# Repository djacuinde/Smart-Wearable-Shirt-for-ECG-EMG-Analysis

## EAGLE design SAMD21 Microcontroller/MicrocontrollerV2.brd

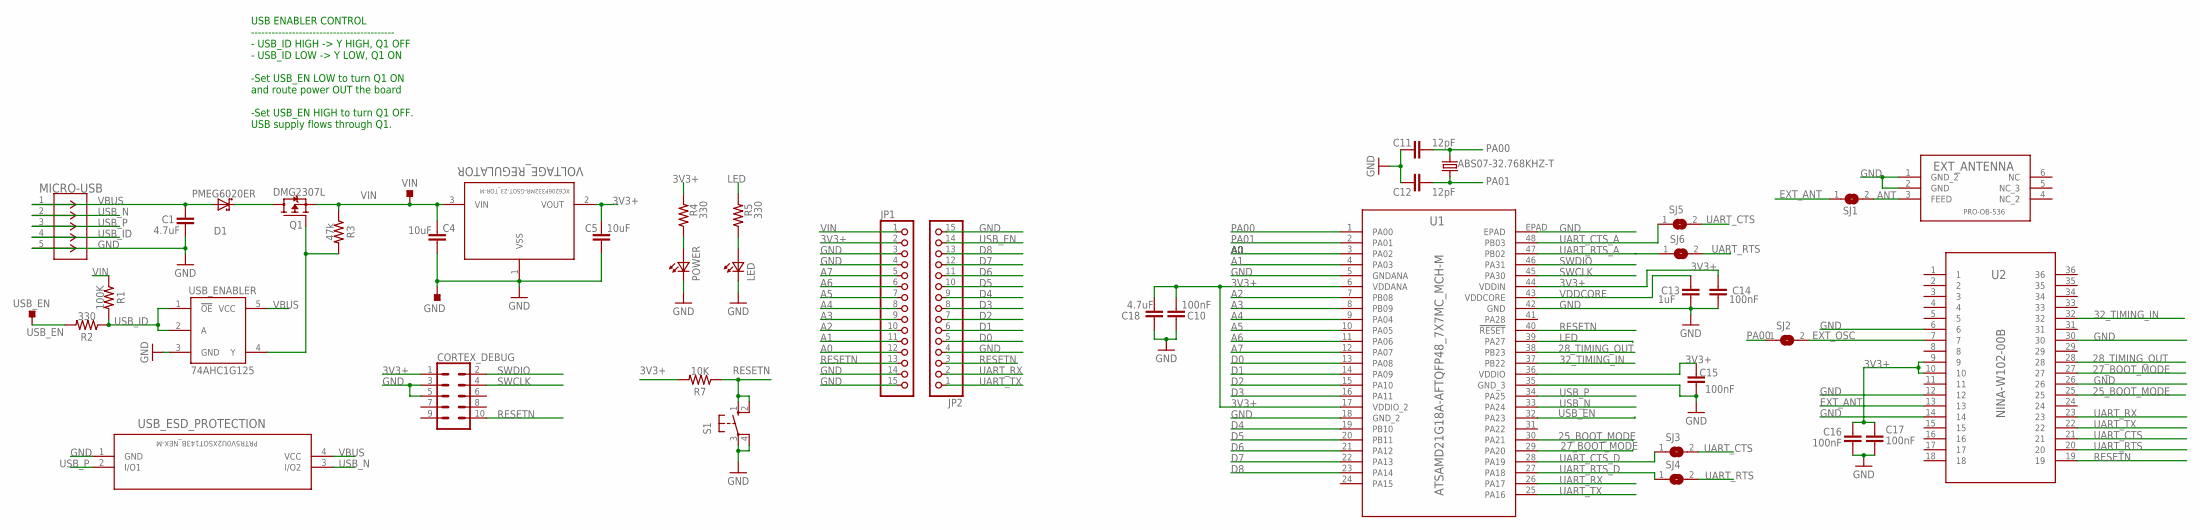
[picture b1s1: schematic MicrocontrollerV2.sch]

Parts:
ABS07-32.768KHZ-T: 32.768KHz; ABS07-32.768KHZ-T
C1, C18: 4.7uF; CAPC1608X85
C4, C5: 10uF; CAPC1608X85
C10, C14, C15, C16, C17: 100nF; CAPC1608X85
C11, C12: 12pF; CAPC1608X85
C13: 1uF; CAPC1608X85
CORTEX_DEBUG: CONN_05X2NO_SILK; 2X5_NOSILK
D1: PMEG6020ER; SOD123W
EXT_ANTENNA: PRO-OB-536; PRO-OB-536_PAB
GND: TESTPOINT_TPS-SMD-10SN; TESTPOINT_SMD-10SN
JP1, JP2: PINHD-1X15; 1X15
LED: HSMR-C190; 0603
MICRO-USB: ZX62-AB-5PA(31); CONN5_ZX62-AB-5PA_HIR
POWER: HSMR-C190; 0603
Q1: DMG2307L; SOT96P240X110-3N
R1: 100K; RESC1608X60
R2, R4, R5: 330; RESC1608X60
R3: 47k; RESC1608X60
R7: 10K; RESC1608X60
S1: PTS525SK08; SM08
SJ1, SJ2, SJ3, SJ4, SJ5, SJ6: SJ
U1: ATSAMD21G18A-AFTQFP48_7X7MC_MCH-M; TQFP48_7X7MC_MCH-M
U2: NINA-W102-00B; QFN_W151-00B_UBL
USB_EN: TESTPOINT_TPS-SMD-10SN; TESTPOINT_SMD-10SN
USB_ENABLER: 74AHC1G125; SOT23-5L
USB_ESD_PROTECTION: PRTR5V0U2XSOT143B_NEX-M; SOT143B_NEX-M
VIN: TESTPOINT_TPS-SMD-10SN; TESTPOINT_SMD-10SN
VOLTAGE_REGULATOR: XC6206P332MR-GSOT-23_TOR-M; SOT-23_TOR-M

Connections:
3V3+: C5.1, C10.2, C14.2, C15.2, C16.1, C17.2, C18.2, CORTEX_DEBUG.1, JP1.2, R4.2, R7.2, U1.6 (VDDANA), U1.17 (VDDIO_2), U1.36 (VDDIO), U1.44 (VDDIN), U2.9, U2.10, VOLTAGE_REGULATOR.2 (VOUT)
25_BOOT_MODE: U1.30 (PA21), U2.25
27_BOOT_MODE: U1.29 (PA20), U2.27
28_TIMING_OUT: U1.38 (PB23), U2.28
32_TIMING_IN: U1.37 (PB22), U2.32
A0: JP1.12, U1.3 (PA02)
A1: JP1.11, U1.4 (PA03)
A2: JP1.10, U1.7 (PB08)
A3: JP1.9, U1.8 (PB09)
A4: JP1.8, U1.9 (PA04)
A5: JP1.7, U1.10 (PA05)
A6: JP1.6, U1.11 (PA06)
A7: JP1.5, U1.12 (PA07)
ANT: EXT_ANTENNA.3 (FEED), SJ1.2
D0: JP2.5, U1.13 (PA08)
D1: JP2.6, U1.14 (PA09)
D2: JP2.7, U1.15 (PA10)
D3: JP2.8, U1.16 (PA11)
D4: JP2.9, U1.19 (PB10)
D5: JP2.10, U1.20 (PB11)
D6: JP2.11, U1.21 (PA12)
D7: JP2.12, U1.22 (PA13)
D8: JP2.13, U1.23 (PA14)
EXT_ANT: SJ1.1, U2.13
EXT_OSC: SJ2.2, U2.7
GND: C1.2, C4.1, C5.2, C10.1, C11.1, C12.1, C13.1, C14.1, C15.1, C16.2, C17.1, C18.1, CORTEX_DEBUG.3, CORTEX_DEBUG.5, EXT_ANTENNA.1 (GND_2), EXT_ANTENNA.2 (GND), GND.TP, JP1.3, JP1.4, JP1.14, JP1.15, JP2.4, JP2.15, LED.1 (K2), MICRO-USB.5, POWER.1 (K2), S1.3, S1.4 (P1), U1.5 (GNDANA), U1.18 (GND_2), U1.35 (GND_3), U1.42 (GND), U1.EPAD, U2.6, U2.12, U2.14, U2.26, U2.30, USB_ENABLER.3 (GND), USB_ESD_PROTECTION.1 (GND), VOLTAGE_REGULATOR.1 (VSS)
LED: R5.2, U1.39 (PA27)
unnamed: LED.2 (A2), R5.1
unnamed: POWER.2 (A2), R4.1
unnamed: D1.1 (K), Q1.3 (D)
unnamed: Q1.1 (G), R3.2, USB_ENABLER.4 (Y)
PA00: ABS07-32.768KHZ-T.2, C11.2, SJ2.1, U1.1 (PA00)
PA01: ABS07-32.768KHZ-T.1, C12.2, U1.2 (PA01)
RESETN: CORTEX_DEBUG.10, JP1.13, JP2.3, R7.1, S1.1 (S), S1.2 (S1), U1.40 (!RESET), U2.19
SWCLK: CORTEX_DEBUG.4, U1.45 (PA30)
SWDIO: CORTEX_DEBUG.2, U1.46 (PA31)
UART_CTS: SJ3.2, SJ5.2, U2.21
UART_CTS_A: SJ5.1, U1.48 (PB03)
UART_CTS_D: SJ3.1, U1.28 (PA19)
UART_RTS: SJ4.2, SJ6.2, U2.20
UART_RTS_A: SJ6.1, U1.47 (PB02)
UART_RTS_D: SJ4.1, U1.27 (PA18)
UART_RX: JP2.2, U1.26 (PA17), U2.23
UART_TX: JP2.1, U1.25 (PA16), U2.22
USB_EN: JP2.14, R2.2, U1.32 (PA23), USB_EN.TP
USB_ID: MICRO-USB.4, R1.2, R2.1, USB_ENABLER.1 (!OE), USB_ENABLER.2 (A)
USB_N: MICRO-USB.2, U1.33 (PA24), USB_ESD_PROTECTION.3 (I/O2)
USB_P: MICRO-USB.3, U1.34 (PA25), USB_ESD_PROTECTION.2 (I/O1)
VBUS: C1.1, D1.2 (A), MICRO-USB.1, USB_ENABLER.5 (VCC), USB_ESD_PROTECTION.4 (VCC)
VDDCORE: C13.2, U1.43 (VDDCORE)
VIN: C4.2, JP1.1, Q1.2 (S), R1.1, R3.1, VIN.TP, VOLTAGE_REGULATOR.3 (VIN)

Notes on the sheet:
USB ENABLER CONTROL ------------------------------------------ - USB_ID HIGH -> Y HIGH, Q1 OFF - USB_ID LOW -> Y LOW, Q1 ON -Set USB_EN LOW to turn Q1 ON and route power OUT the board -Set USB_EN HIGH to turn Q1 OFF. USB supply flows through Q1.

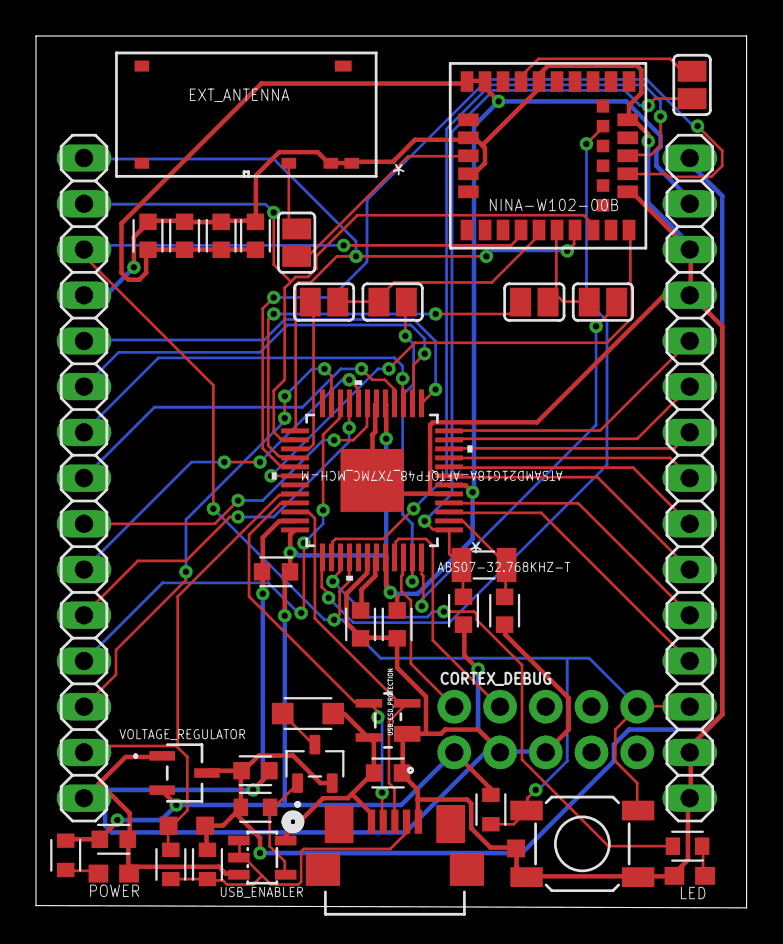
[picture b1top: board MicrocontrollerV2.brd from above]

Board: 2 copper layers, 39.5 x 48.4 mm, 43 parts (0 on the bottom side), 51 nets.

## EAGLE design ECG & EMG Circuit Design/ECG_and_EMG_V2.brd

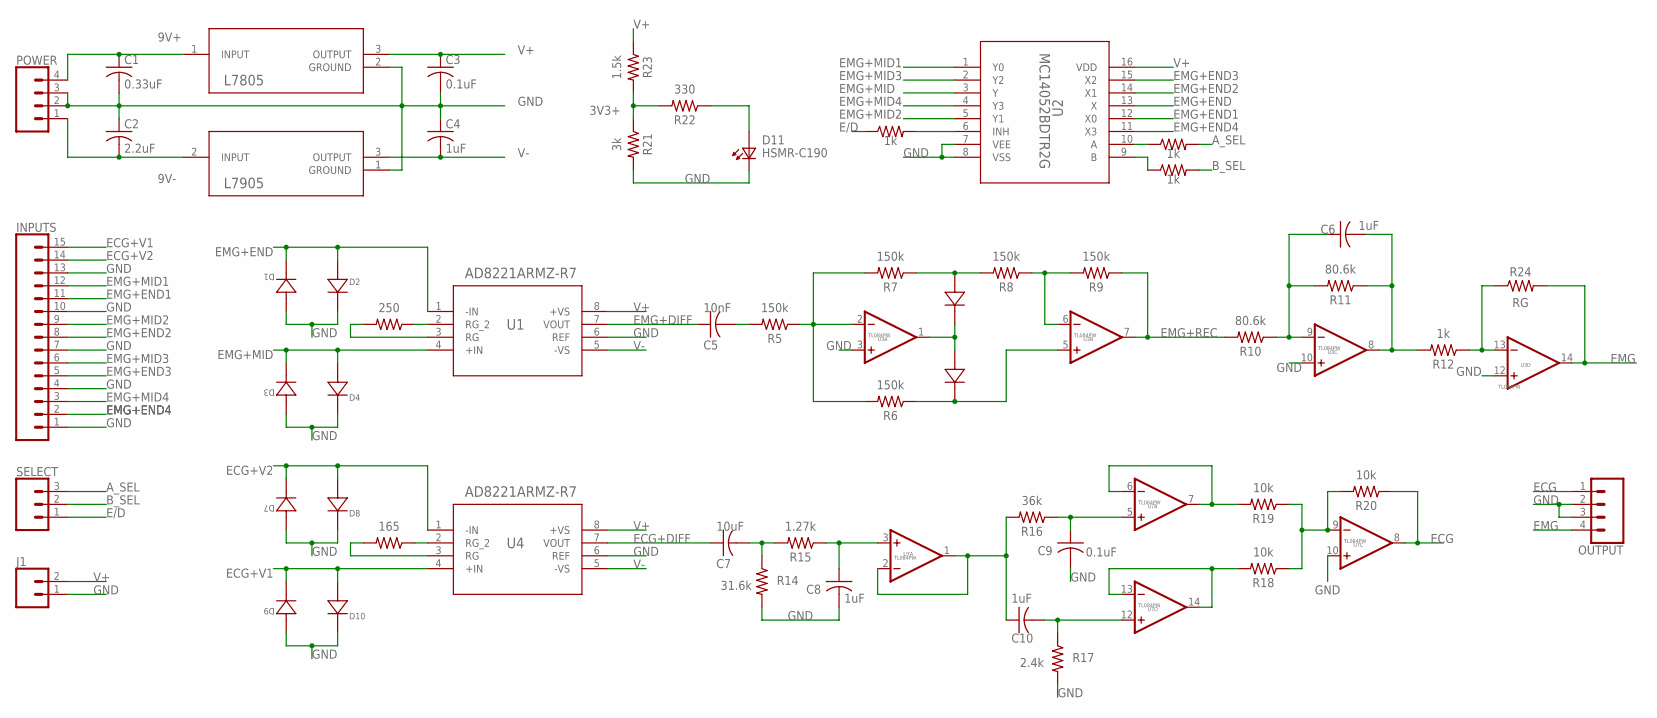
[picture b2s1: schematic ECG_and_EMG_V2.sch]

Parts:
C1: 0.33uF; CAPC2012X110
C2: 2.2uF; CAPC2012X110
C3, C9: 0.1uF; CAPC2012X110
C4, C6, C8, C10: 1uF; CAPC2012X110
C5: 10nF; CAPC2012X110
C7: 10uF; CAPC2012X110
D1, D2, D3, D4, D5, D6, D7, D8, D9, D10: 1N4148W-V-GS08SOD123_VIS-L; SOD123_VIS-L
D11: HSMR-C190; 0603
INPUTS: CONN_15; 1X15
J1: CONN_02; 1X02
L7805: L7805CD2T-TRD2PAK_STM-M; D2PAK_STM-M
L7905: L7905ACD2T-TRD2PAK_STM-M; D2PAK_STM-M
OUTPUT: CONN_04; 1X04
POWER: CONN_04; 1X04
R1, R2, R3, R12: 1k; RESC2012X65
R4: 250; RESC2012X65
R5, R6, R7, R8, R9: 150k; RESC2012X65
R10, R11: 80.6k; RESC2012X65
R13: 165; RESC2012X65
R14: 31.6k; RESC2012X65
R15: 1.27k; RESC2012X65
R16: 36k; RESC2012X65
R17: 2.4k; RESC2012X65
R18, R19, R20: 10k; RESC2012X65
R21: 3k; RESC2012X65
R22: 330; RESC2012X65
R23: 1.5k; RESC2012X65
R24: RG; RESC2012X65
SELECT: CONN_03; 1X03
U1, U4: AD8221ARMZ-R7; RM_8_ADI
U2: MC14052BDTR2G; TSSOP-16_ONS
U3, U7: TL084PW; TSSOP14

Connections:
3V3+: R21.1, R22.2, R23.2
9V+: C1.1, L7805.1 (INPUT), POWER.4
9V-: C2.2, L7905.2 (INPUT), POWER.1
A_SEL: R2.2, SELECT.3
B_SEL: R3.2, SELECT.2
E/D: R1.1, SELECT.1
ECG: OUTPUT.1, R20.1, U7.8 (OUT)
ECG+DIFF: C7.1, U4.7 (VOUT)
ECG+V1: D9.1, D10.2, INPUTS.15, U4.4 (+IN)
ECG+V2: D7.1, D8.2, INPUTS.14, U4.1 (-IN)
EMG: OUTPUT.4, R24.2, U3.14 (OUT)
EMG+DIFF: C5.1, U1.7 (VOUT)
EMG+END: D1.1, D2.2, U1.1 (-IN), U2.13 (X)
EMG+END1: INPUTS.11, U2.12 (X0)
EMG+END2: INPUTS.8, U2.14 (X1)
EMG+END3: INPUTS.5, U2.15 (X2)
EMG+END4: INPUTS.2, U2.11 (X3)
EMG+MID: D3.1, D4.2, U1.4 (+IN), U2.3 (Y)
EMG+MID1: INPUTS.12, U2.1 (Y0)
EMG+MID2: INPUTS.9, U2.5 (Y1)
EMG+MID3: INPUTS.6, U2.2 (Y2)
EMG+MID4: INPUTS.3, U2.4 (Y3)
EMG+REC: R9.1, R10.2, U3.7 (OUT)
GND: C1.2, C2.1, C3.2, C4.1, C8.2, C9.2, D1.2, D2.1, D3.2, D4.1, D7.2, D8.1, D9.2, D10.1, D11.1 (K2), INPUTS.1, INPUTS.4, INPUTS.7, INPUTS.10, INPUTS.13, J1.1, L7805.2 (GROUND), L7905.1 (GROUND), OUTPUT.2, OUTPUT.3, POWER.2, POWER.3, R14.2, R17.2, R21.2, U1.6 (REF), U2.7 (VEE), U2.8 (VSS), U3.3 (+IN), U3.10 (+IN), U3.12 (+IN), U4.6 (REF), U7.10 (+IN)
unnamed: R1.2, U2.6 (INH)
unnamed: R2.1, U2.10 (A)
unnamed: R3.1, U2.9 (B)
unnamed: R4.1, U1.2 (RG_2)
unnamed: R4.2, U1.3 (RG)
unnamed: C5.2, R5.2
unnamed: R5.1, R6.2, R7.2, U3.2 (-IN)
unnamed: D6.1, R6.1, U3.5 (+IN)
unnamed: D5.1, D6.2, U3.1 (OUT)
unnamed: D5.2, R7.1, R8.2
unnamed: R8.1, R9.2, U3.6 (-IN)
unnamed: C6.1, R10.1, R11.2, U3.9 (-IN)
unnamed: C6.2, R11.1, R12.2, U3.8 (OUT)
unnamed: R13.1, U4.2 (RG_2)
unnamed: R12.1, R24.1, U3.13 (-IN)
unnamed: R13.2, U4.3 (RG)
unnamed: C7.2, R14.1, R15.2
unnamed: C8.1, R15.1, U7.3 (+IN)
unnamed: C10.1, R16.2, U7.1 (OUT), U7.2 (-IN)
unnamed: C9.1, R16.1, U7.5 (+IN)
unnamed: C10.2, R17.1, U7.12 (+IN)
unnamed: R18.2, U7.13 (-IN), U7.14 (OUT)
unnamed: R19.2, U7.6 (-IN), U7.7 (OUT)
unnamed: R18.1, R19.1, R20.2, U7.9 (-IN)
unnamed: D11.2 (A2), R22.1
V+: C3.1, J1.2, L7805.3 (OUTPUT), R23.1, U1.8 (+VS), U2.16 (VDD), U3.4 (V+), U4.8 (+VS), U7.4 (V+)
V-: C4.2, L7905.3 (OUTPUT), U1.5 (-VS), U3.11 (V-), U4.5 (-VS), U7.11 (V-)

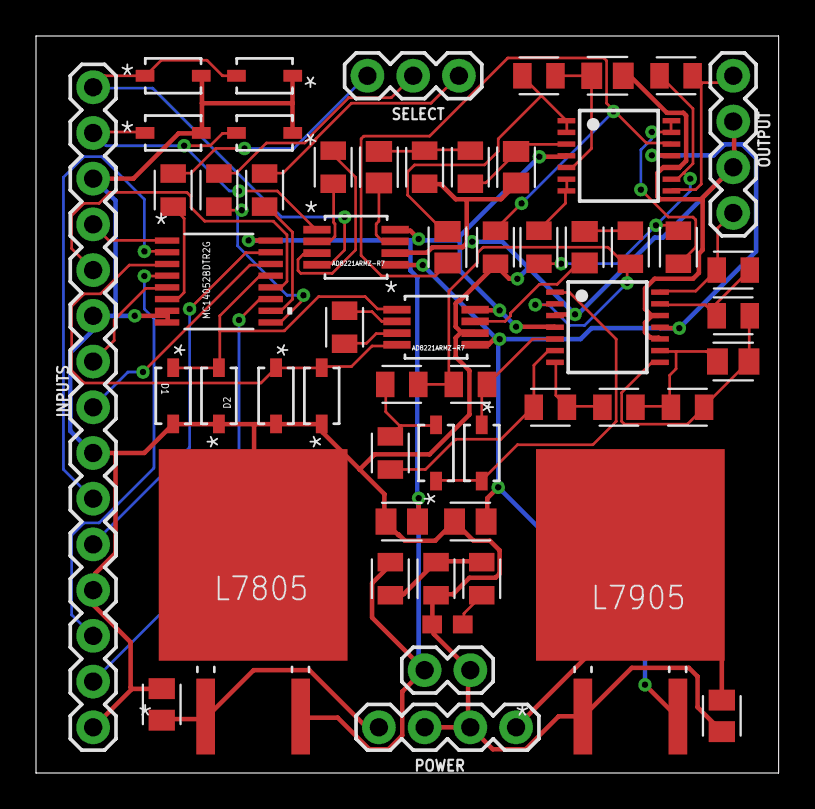
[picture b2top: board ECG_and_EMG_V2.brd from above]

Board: 2 copper layers, 41.3 x 40.9 mm, 57 parts (0 on the bottom side), 51 nets.

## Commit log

2020-12-27 Create EAGLE
2020-12-27 Create SAMD21 Microcontroller
2020-12-27 Create 1
2020-12-27 Rename MicrocontrollerV1.brd to MicrocontrollerV2.brd
2020-12-27 Rename MicrocontrollerV1.sch to MicrocontrollerV2.sch
2020-12-27 Create common

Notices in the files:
parts and their libraries:
SparkFun-Connectors: Licensing: Creative Commons ShareAlike 4.0 International - https://creativecommons.org/licenses/by-sa/4.0
op-amp2: Copyright (C) 2006 by Bob Starr
COPYRIGHT: Copyright (C) 2016 Accelerated Designs. All rights reserved
pts525_10: (c) 2014 Samuel Lourenço
